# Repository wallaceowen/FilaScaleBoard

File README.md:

# FilaScale

This is a small ESP32-based board designed to fit directly behind a standard 2.8" SPI-driven QVGA TFT touchscreen.
It was built to the requirements of a filament monitoring device.  The board provides:

* Humidity, temperature and weight monitoring of a spool of filament in a drybox
* RFID tag reader
* QVGA display with touchscreen for user interface
* SDCard for logging, local configuration
* Expansion interfaces (two SPI, one I2C, and four uncommitted GPIO on two separate headers)
* Serial communications with a host
* Wifi and bluetooth connectivity

## The board (KiCAD rendering)

## The firmware
The board runs code for monitoring the humidity and weight of a spool of 3D printer filament in a drybox.
  [GitHub](https://github.com/wallaceowen/FilaScale/tree/master)
The code is C++, and uses the simple Arduino toolchain.

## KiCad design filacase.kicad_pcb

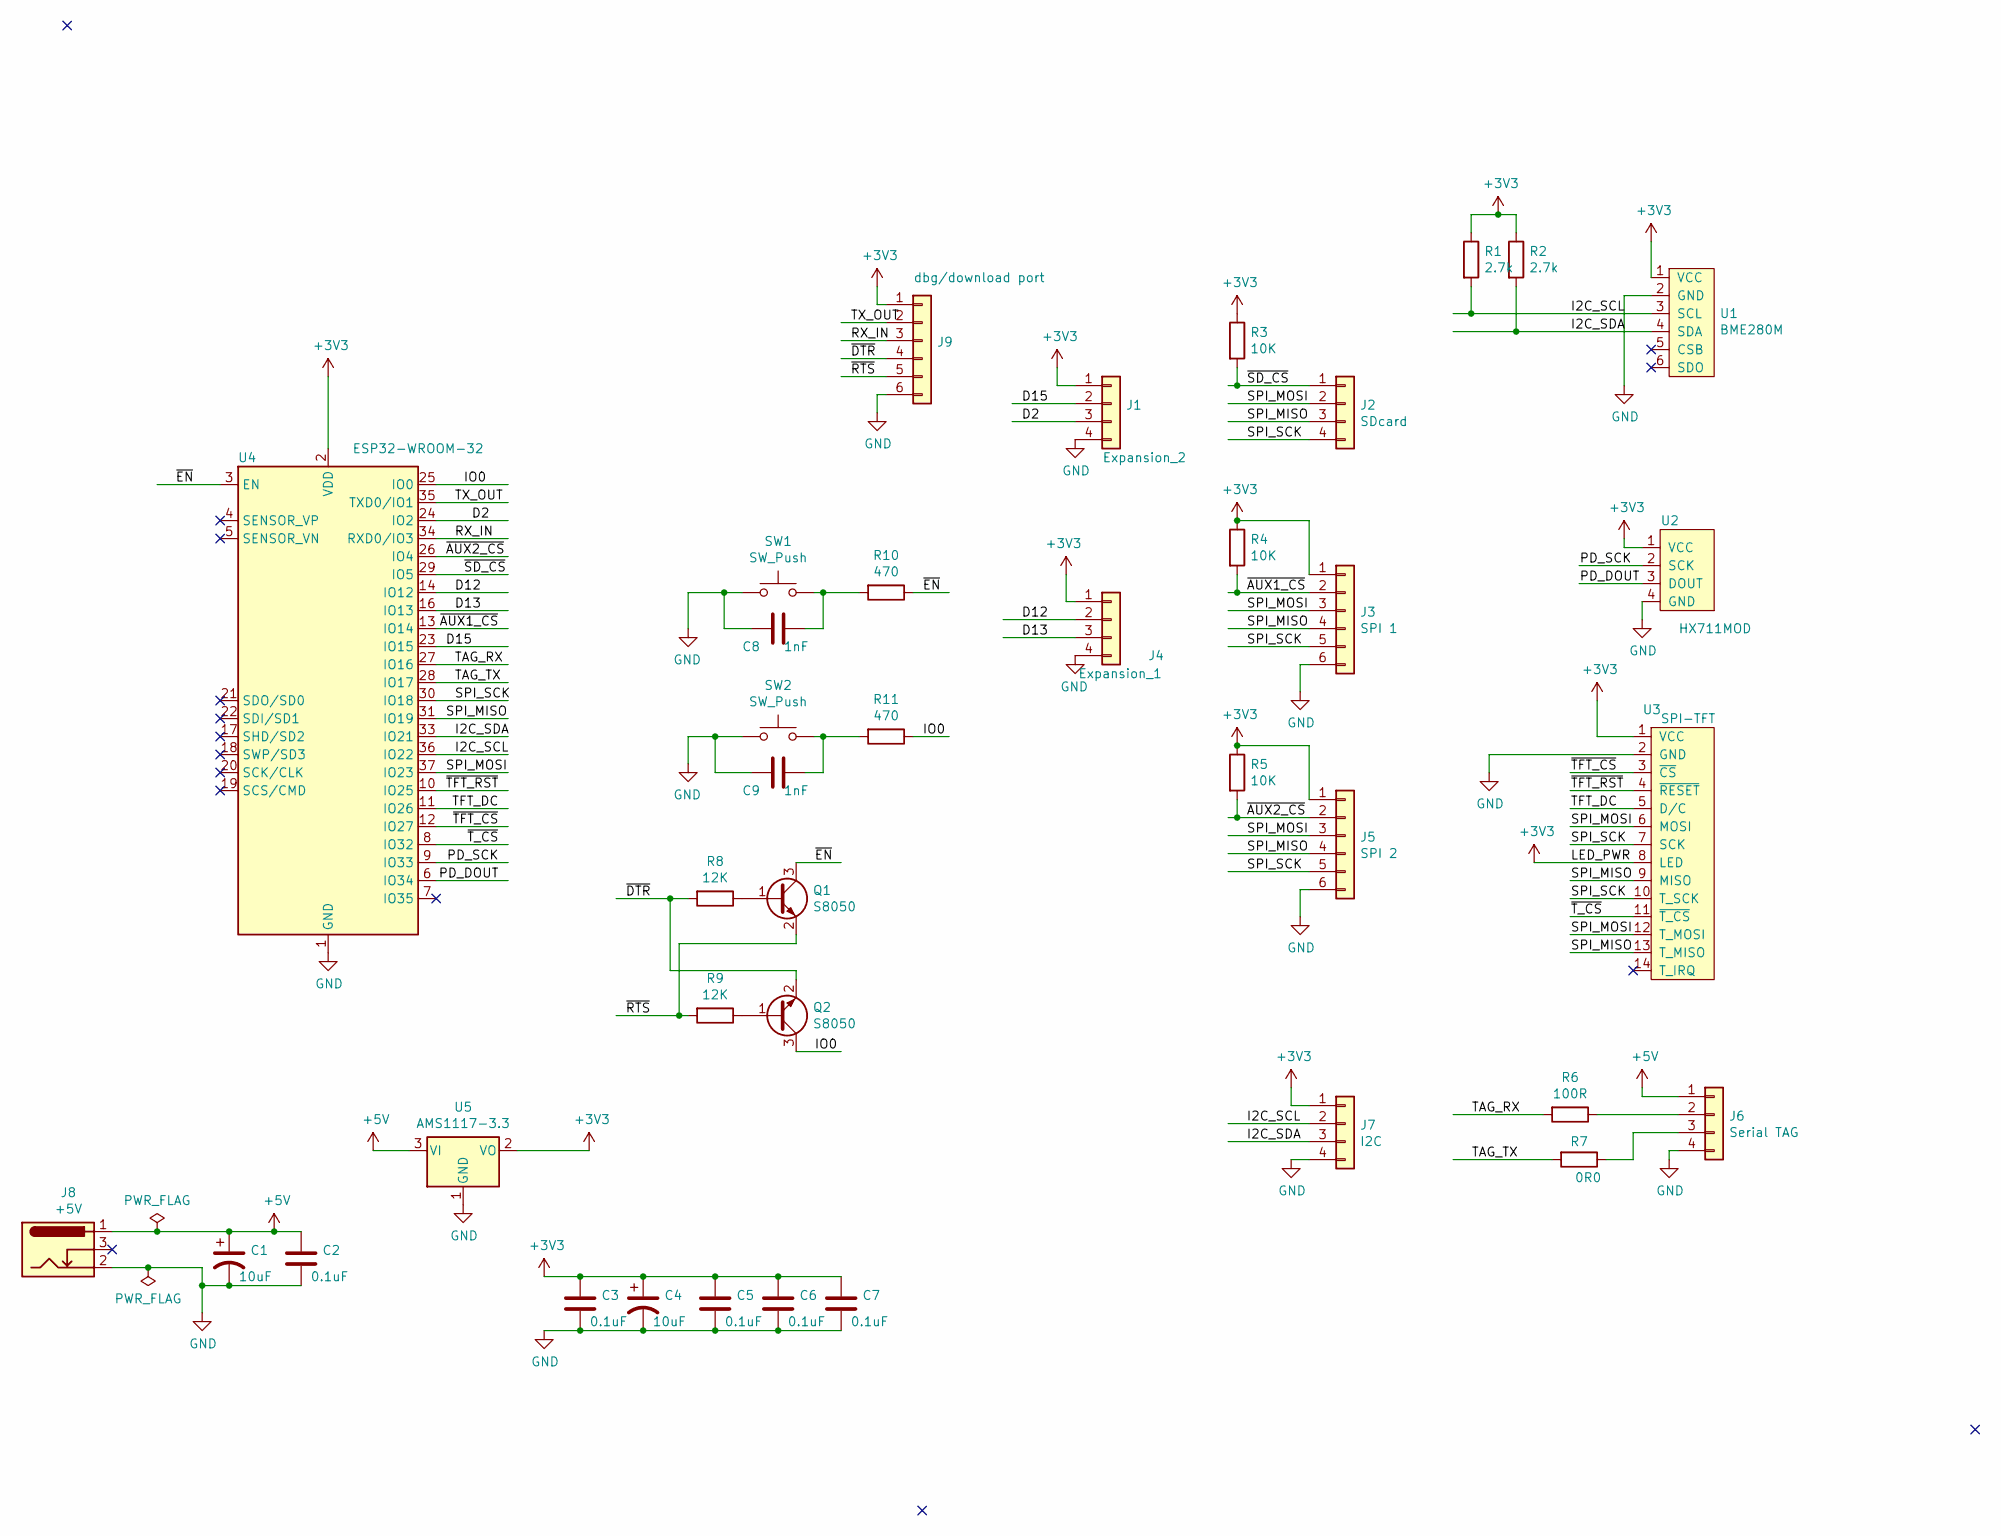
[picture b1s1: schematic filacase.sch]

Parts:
C1, C4: 10uF; C_2220_5650Metric_Pad1.97x5.40mm_HandSolder
C2, C3, C5, C6, C7: 0.1uF; C_0805_2012Metric
C8, C9: 1nF; C_0805_2012Metric
J1: Expansion_2; PinHeader_1x04_P2.54mm_Vertical
J2: SDcard; PinSocket_1x04_P2.54mm_Vertical
J3: SPI 1; PinHeader_1x06_P2.54mm_Vertical
J4: Expansion_1; PinHeader_1x04_P2.54mm_Vertical
J5: SPI 2; PinHeader_1x06_P2.54mm_Vertical
J6: Serial TAG; PinHeader_1x04_P2.54mm_Vertical
J7: I2C; PinHeader_1x04_P2.54mm_Vertical
J8: +5V; BarrelJack_Horizontal
J9: dbg/download port; PinHeader_1x06_P2.54mm_Vertical
Q1, Q2: S8050; SOT-23
R1, R2: 2.7k; R_0603_1608Metric
R3, R4, R5: 10K; R_0805_2012Metric
R6: 100R; R_0603_1608Metric
R7: 0R0; R_0603_1608Metric
R8, R9: 12K; R_0603_1608Metric
R10, R11: 470; R_0805_2012Metric
SW1, SW2: SW_Push; SW_Push_1P1T_NO_CK_KSC6xxJ
U1: BME280M; PinHeader_1x06_P2.54mm_Vertical
U2: HX711MOD; PinHeader_1x04_P2.54mm_Vertical
U3: SPI-TFT; PinSocket_1x14_P2.54mm_Vertical
U4: ESP32-WROOM-32
U5: AMS1117-3.3; SOT-223-3_TabPin2

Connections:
+3V3: C3.1, C4.1, C5.1, C6.1, C7.1, J1.1, J3.1, J4.1, J5.1, J7.1, J9.1, R1.1, R2.1, R3.1, R4.1, R5.1, U1.1 (VCC), U2.1 (VCC), U3.1 (VCC), U3.8 (LED), U4.2 (VDD), U5.2 (VO)
+5V: C1.1, C2.1, J6.1, J8.1, U5.3 (VI)
/D2: J1.3, U4.24 (IO2)
/D12: J4.2, U4.14 (IO12)
/D13: J4.3, U4.16 (IO13)
/D15: J1.2, U4.23 (IO15)
/I2C_SCL: J7.2, R1.2, U1.3 (SCL), U4.36 (IO22)
/I2C_SDA: J7.3, R2.2, U1.4 (SDA), U4.33 (IO21)
/IO0: Q2.3 (C), R11.1, U4.25 (IO0)
/PD_DOUT: U2.3 (DOUT), U4.6 (IO34)
/PD_SCK: U2.2 (SCK), U4.9 (IO33)
/RX_IN: J9.3, U4.34 (RXD0/IO3)
/SPI_MISO: J2.3, J3.4, J5.4, U3.9 (MISO), U3.13 (T_MISO), U4.31 (IO19)
/SPI_MOSI: J2.2, J3.3, J5.3, U3.6 (MOSI), U3.12 (T_MOSI), U4.37 (IO23)
/SPI_SCK: J2.4, J3.5, J5.5, U3.7 (SCK), U3.10 (T_SCK), U4.30 (IO18)
/TAG_RX: R6.2, U4.27 (IO16)
/TAG_TX: R7.2, U4.28 (IO17)
/TFT_DC: U3.5 (D/C), U4.11 (IO26)
/TX_OUT: J9.2, U4.35 (TXD0/IO1)
/~AUX1_CS~: J3.2, R4.2, U4.13 (IO14)
/~AUX2_CS~: J5.2, R5.2, U4.26 (IO4)
/~DTR~: J9.4, Q2.2 (E), R8.2
/~EN~: Q1.3 (C), R10.1, U4.3 (EN)
/~RTS~: J9.5, Q1.2 (E), R9.2
/~SD_CS~: J2.1, R3.2, U4.29 (IO5)
/~TFT_CS~: U3.3 (~CS~), U4.12 (IO27)
/~TFT_RST~: U3.4 (~RESET~), U4.10 (IO25)
/~T_CS~: U3.11 (~T_CS~), U4.8 (IO32)
GND: C1.2, C2.2, C3.2, C4.2, C5.2, C6.2, C7.2, C8.2, C9.2, J1.4, J3.6, J4.4, J5.6, J6.4, J7.4, J8.2, J9.6, SW1.1, SW2.1, U1.2 (GND), U2.4 (GND), U3.2 (GND), U4.1 (GND), U4.15 (GND), U4.38 (GND), U4.39 (GND), U5.1 (GND); also elsewhere on the board
unnamed: C8.1, R10.2, SW1.2
unnamed: C9.1, R11.2, SW2.2
unnamed: J6.2, R6.1
unnamed: J6.3, R7.1
unnamed: Q1.1 (B), R8.1
unnamed: Q2.1 (B), R9.1

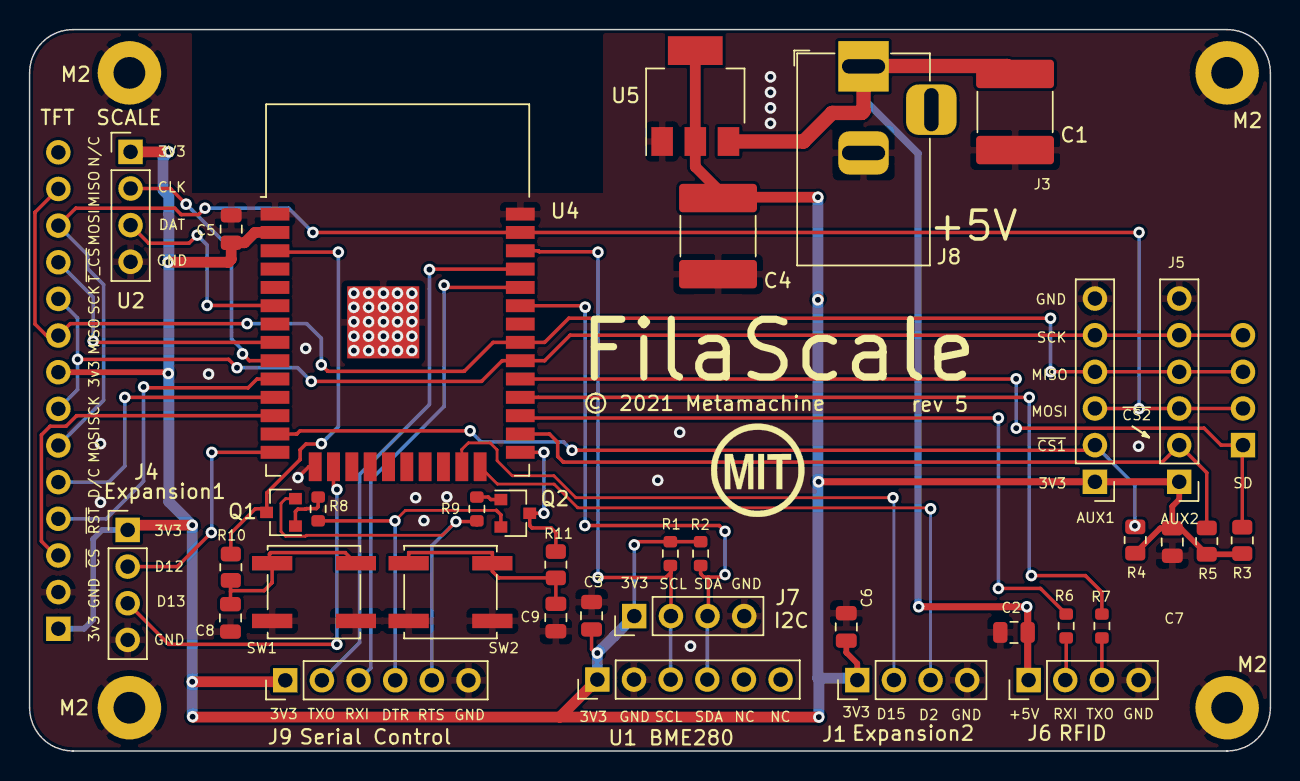
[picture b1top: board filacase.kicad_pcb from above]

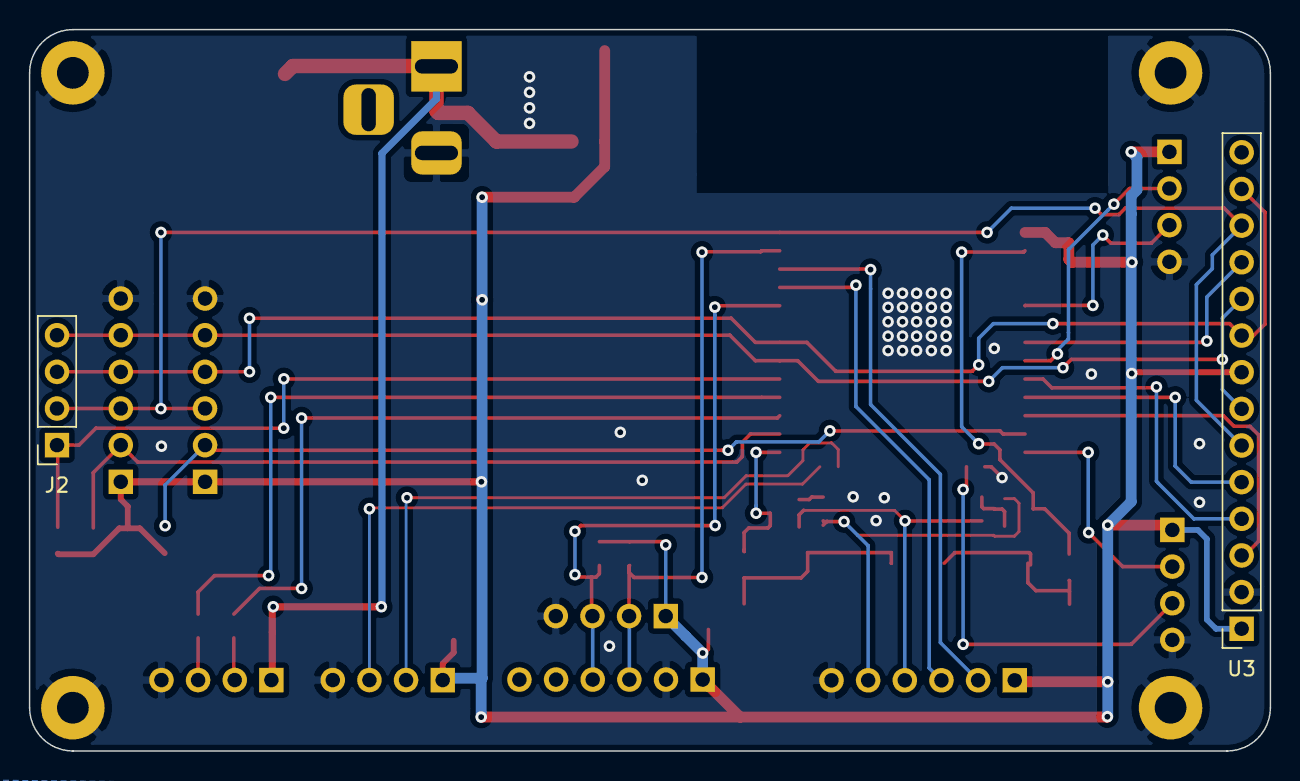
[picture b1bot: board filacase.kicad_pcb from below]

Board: 2 copper layers, 86.0 x 50.0 mm, 42 parts (2 on the bottom side), 35 nets.

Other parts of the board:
M2, M2#2, M2#3, M2#4: MountingHole_2.2mm_M2_Pad

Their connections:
GND: M2.1, M2#2.1, M2#3.1, M2#4.1; also elsewhere on the board

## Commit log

2021-09-18 FilaScaleBoard KiCAD files
2021-09-19 Added pic of board and
2021-09-19 fix readme
2021-09-19 update readme again
2021-09-19 More README updates
2021-09-19 Add a .gitignore; Update the readme
2021-09-25 Flip TFT connector around the right way
2021-09-25 Tweak the layout of a couple of tracks
2021-09-25 Flipped the display connector and SDCARD connector pads because flipping the connectors to the back of the board also flipped the pins up/down.
2021-09-25 Generate a new render of the board; move a couple of traces and rebuild the pours

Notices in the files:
filacase.kicad_pcb:
© 2021 Metamachine
